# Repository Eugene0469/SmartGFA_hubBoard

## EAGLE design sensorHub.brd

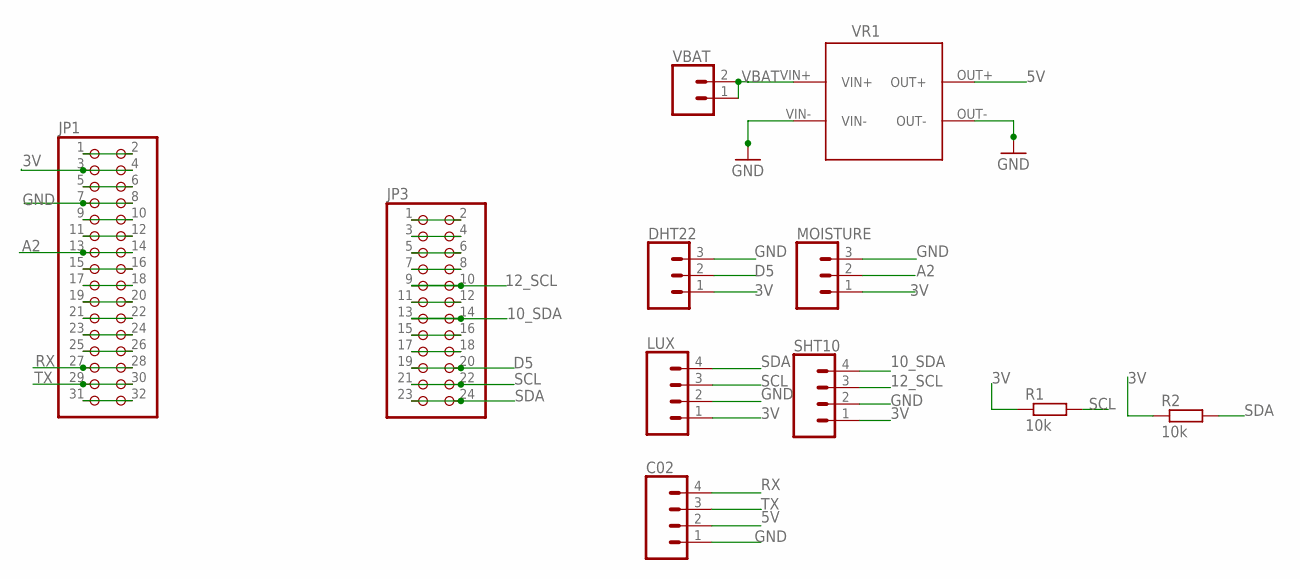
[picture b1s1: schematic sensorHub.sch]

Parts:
C02: CONN_04SCREW; SCREWTERMINAL-3.5MM-4
DHT22: CONN_03SCREW; SCREWTERMINAL-3.5MM-3
JP1: PINHD-2X16; 2X16
JP3: PINHD-2X12; 2X12
LUX: CONN_04SCREW; SCREWTERMINAL-3.5MM-4
MOISTURE: CONN_03SCREW; SCREWTERMINAL-3.5MM-3
R1, R2: 10k; 0207/10
SHT10: CONN_04SCREW; SCREWTERMINAL-3.5MM-4
VBAT: CONN_02; 1X02
VR1: MT3608THROUGH_HOLE; MT3608

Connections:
3V: DHT22.1, JP1.3, JP1.4, LUX.1, MOISTURE.1, R1.1, R2.1, SHT10.1
5V: C02.2, VR1.OUT+
10_SDA: JP3.13, JP3.14, SHT10.4
12_SCL: JP3.9, JP3.10, SHT10.3
A2: JP1.13, JP1.14, MOISTURE.2
D5: DHT22.2, JP3.19, JP3.20
GND: C02.1, DHT22.3, JP1.7, JP1.8, LUX.2, MOISTURE.3, SHT10.2, VR1.OUT-, VR1.VIN-
unnamed: JP1.1, JP1.2
unnamed: JP3.1, JP3.2
unnamed: JP1.5, JP1.6
unnamed: JP3.3, JP3.4
unnamed: JP1.9, JP1.10
unnamed: JP1.11, JP1.12
unnamed: JP3.5, JP3.6
unnamed: JP1.15, JP1.16
unnamed: JP1.17, JP1.18
unnamed: JP1.19, JP1.20
unnamed: JP1.21, JP1.22
unnamed: JP1.23, JP1.24
unnamed: JP1.25, JP1.26
unnamed: JP3.7, JP3.8
unnamed: JP3.11, JP3.12
unnamed: JP1.31, JP1.32
unnamed: JP3.15, JP3.16
unnamed: JP3.17, JP3.18
RX: C02.4, JP1.27, JP1.28
SCL: JP3.21, JP3.22, LUX.3, R1.2
SDA: JP3.23, JP3.24, LUX.4, R2.2
TX: C02.3, JP1.29, JP1.30
VBAT: VBAT.1, VBAT.2, VR1.VIN+

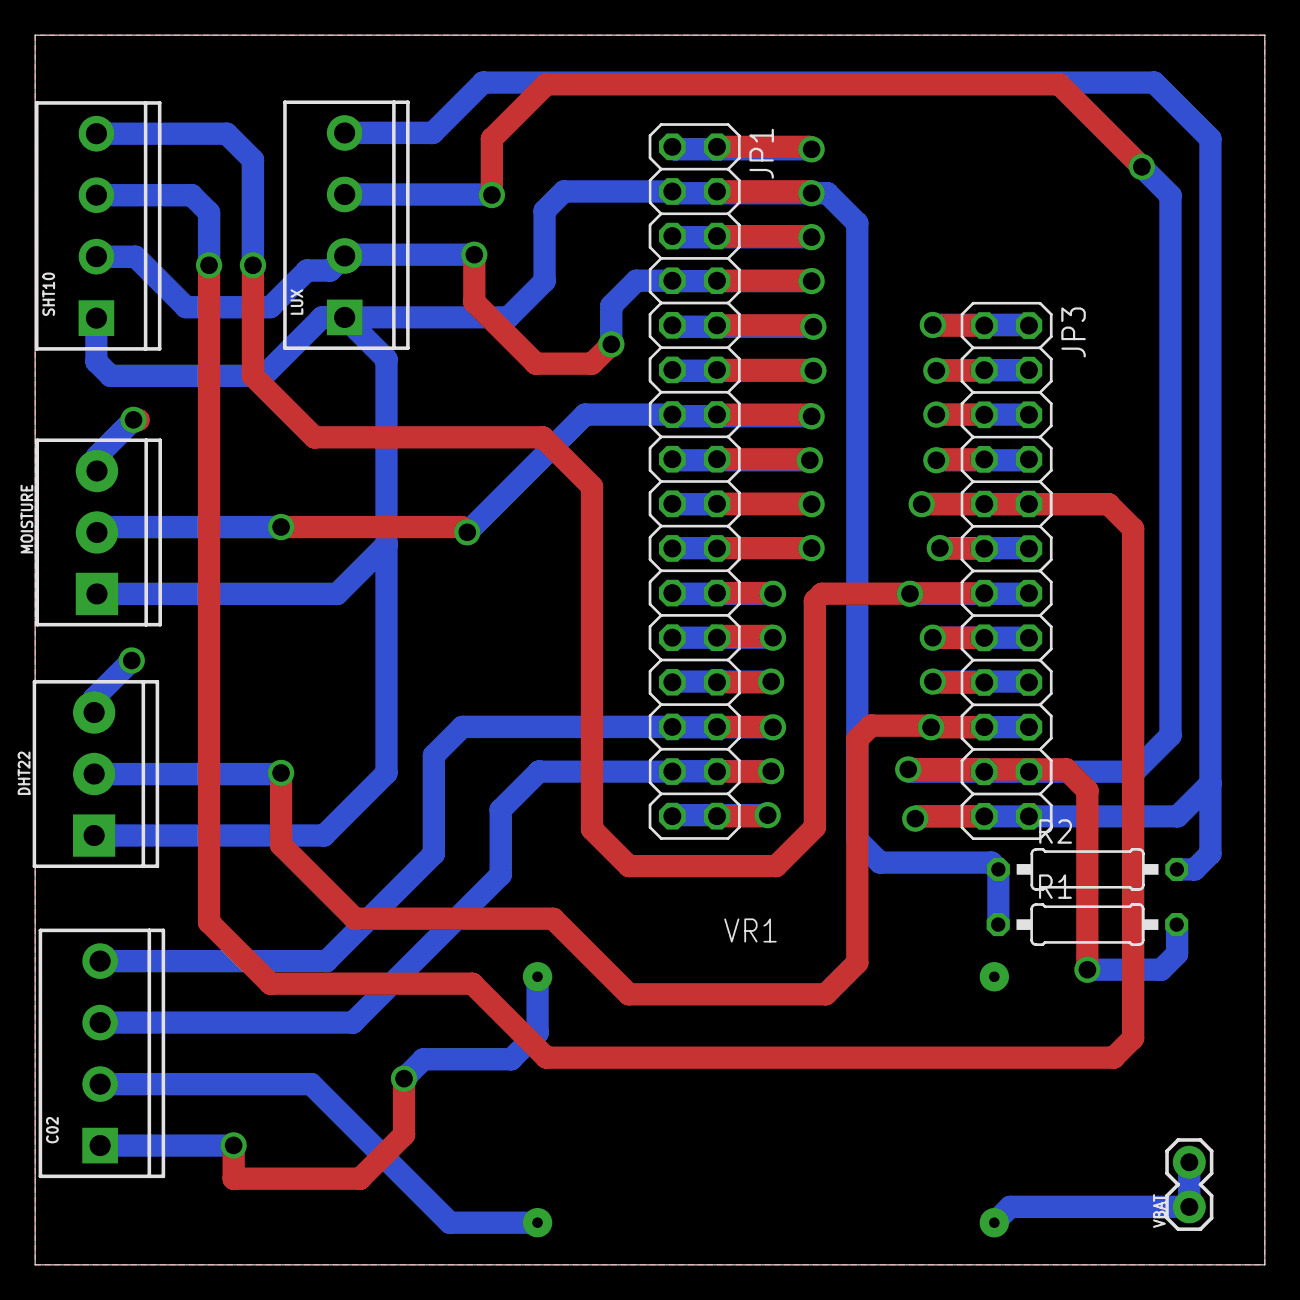
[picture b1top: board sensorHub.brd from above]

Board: 2 copper layers, 70.0 x 70.0 mm, 11 parts (0 on the bottom side), 30 nets.

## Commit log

2020-08-29 Create LICENSE
2020-08-29 Adds the feather m0 to schematic
2020-08-29 Adds the lm2577 and two pull up resistors to the shematic
2020-08-29 Adds connector pins for the sensors to the schematic
2020-08-29 Completes connections in the schematic
2020-08-29 Places components in pcb brd layout
2020-09-01 Set components in place in brd file
2020-09-01 Deletes the feather board
2020-09-01 Completes the brd file
2020-09-01 Connects the sht10 pins from SDA and SCL to pin 10 and pin 12 respectively
2020-09-01 Transfers the sht schematic changes to the brd file
2020-09-05 Reroutes the connection between the double female header pins
2020-09-05 Completes the rerouting of the sensor hub board
2020-09-05 Adjusts routes in brd file(mistake)
2020-09-05 Replaces the 22 double header with the 24 double header

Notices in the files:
parts and their libraries:
SparkFun-Connectors: Licensing: Creative Commons ShareAlike 4.0 International - https://creativecommons.org/licenses/by-sa/4.0
